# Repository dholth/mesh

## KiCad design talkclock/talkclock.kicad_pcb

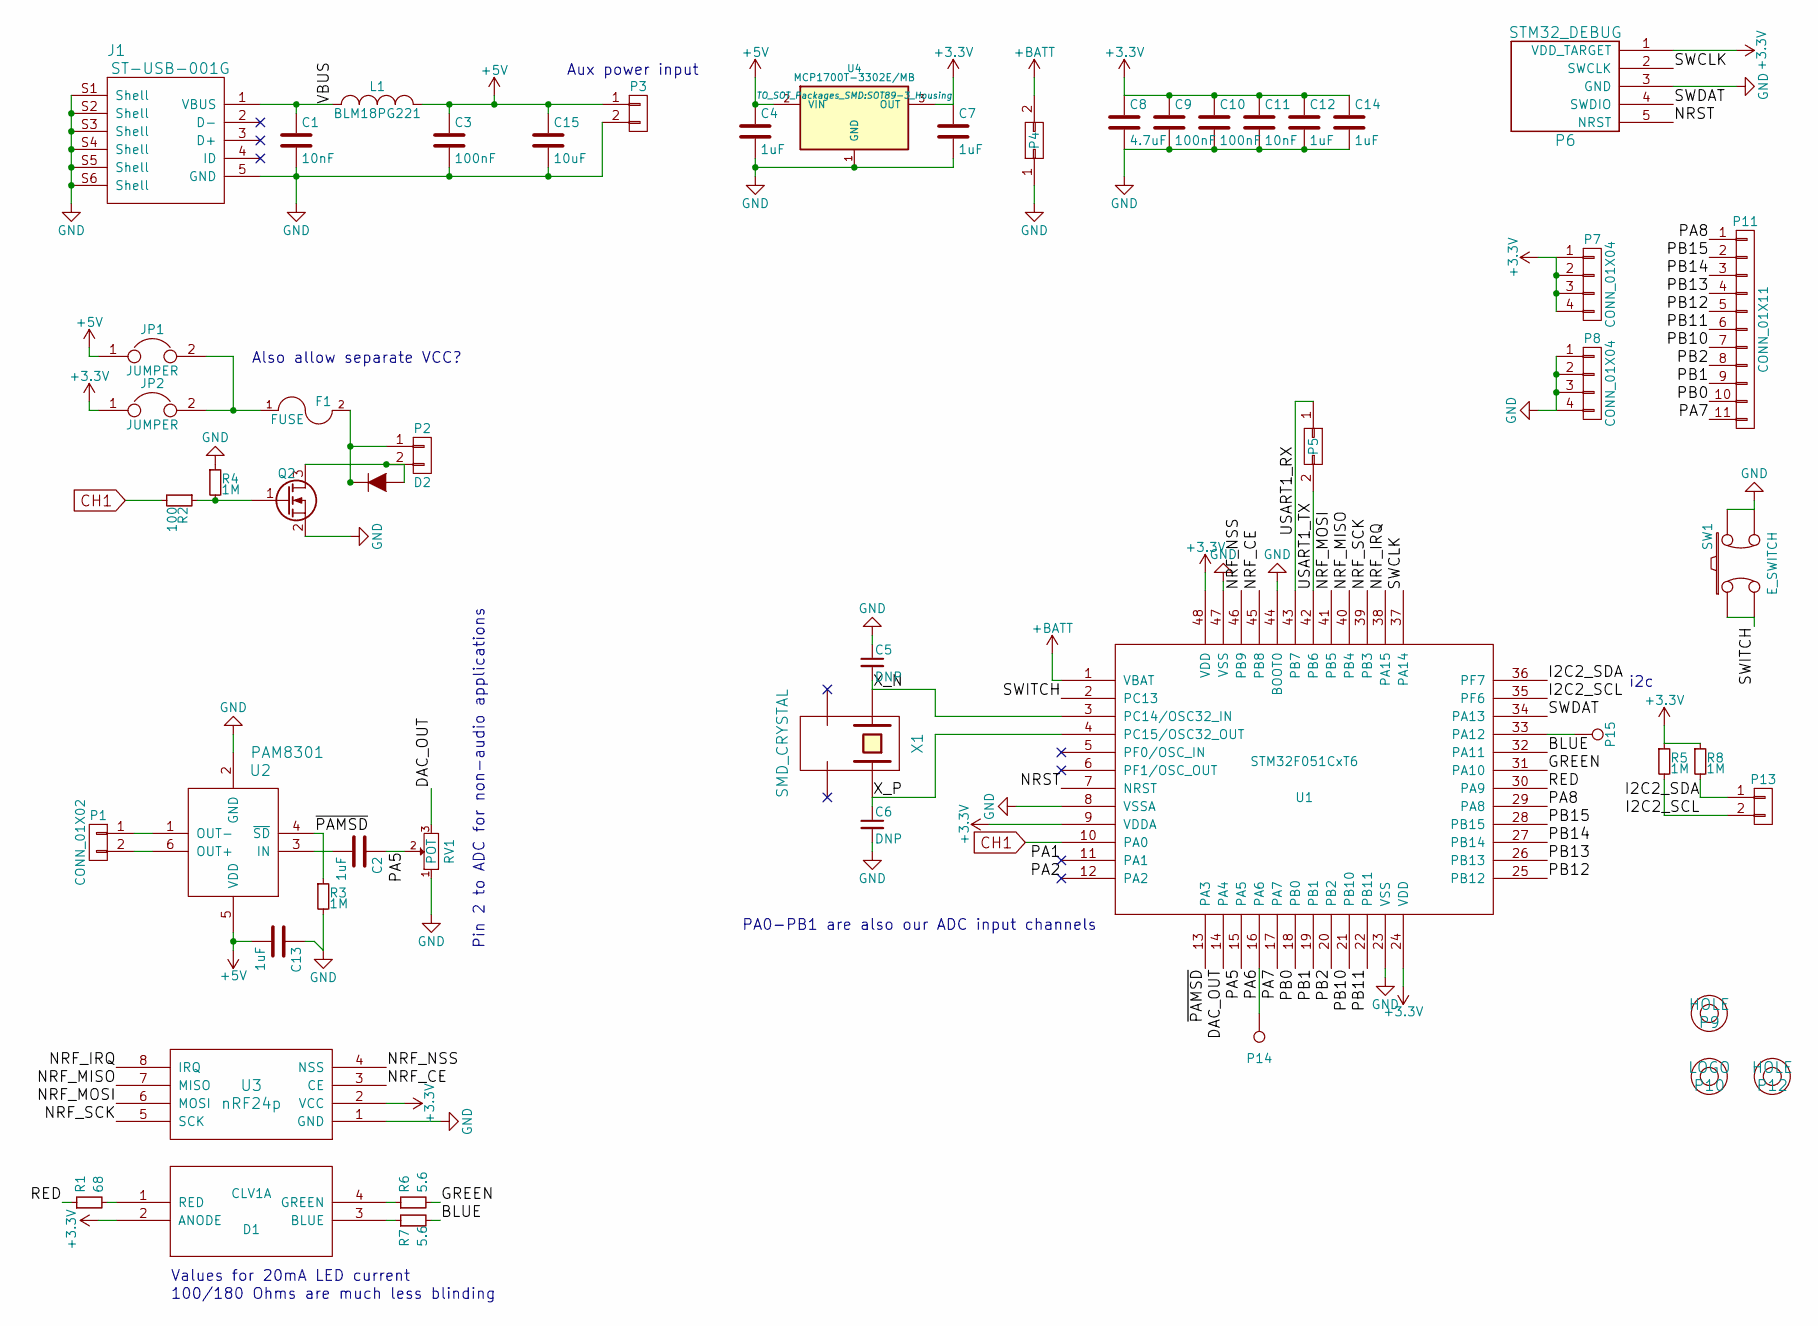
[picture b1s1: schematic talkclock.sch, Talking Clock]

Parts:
C1, C11: 10nF; C_0603
C2, C4, C7, C12, C13, C14: 1uF; C_0603
C3, C9, C10: 100nF; C_0603
C5, C6: DNP; C_0603
C8: 4.7uF; C_1206
C15: 10uF; C_Radial_D5_L11_P2
D1: CLV1A; CREE4
D2: 1N4448; SOD-323-SKYWORKS
F1: FUSE; R_1206
J1: ST-USB-001G; SUNTECH_ST-USB-001G
JP1, JP2: JUMPER; SB
L1: BLM18PG221; R_0805
P1, P13: CONN_01X02; Pin_Header_Straight_1x02
P2, P3: CONN_01X02; JST-S2B-PH
P4: CONN_02X01; BAT-HLD-012-SMT
P5: CONN_02X01; Pin_Header_Straight_1x02
P6: STM32_DEBUG; Pin_Header_Straight_1x05
P7, P8: CONN_01X04; Pin_Header_Straight_1x04
P9, P12: HOLE; MountingHole_3-2mm_DP
P10: LOGO
P11: CONN_01X11; Pin_Header_Straight_1x11
P14, P15: TEST_1P; Pin_Header_Straight_1x01_Small
Q2: Q_NMOS_GSD; SOT-23
R1: 68; R_0603
R2: 100; R_0603
R3, R4, R5, R8: 1M; R_0603
R6, R7: 5.6; R_0603
RV1: POT; EVU-F3A
SW1: E_SWITCH
U1: STM32F051CxT6; LQFP-48_7x7mm_Pitch0.5mm
U2: PAM8301; SOT-23-6
U3: nRF24p; nRF24
U4: MCP1700T-3302E/MB; SOT89-3_Housing
X1: SMD_CRYSTAL; CM200C

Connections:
+3V3: C7.1, C8.1, C9.1, C10.1, C11.1, C12.1, C14.1, D1.2 (ANODE), JP2.1, P6.1 (VDD_TARGET), P7.1, P7.2, P7.3, P7.4, R5.1, R8.1, U1.9 (VDDA), U1.24 (VDD), U1.48 (VDD), U3.2 (VCC), U4.3 (OUT)
+5V: C3.1, C4.1, C13.2, C15.1, JP1.1, L1.2, P3.1, U2.5 (VDD), U4.2 (VIN)
+BATT: P4.2, U1.1 (VBAT)
/BLUE: R7.2, U1.32 (PA11)
/DAC_OUT: RV1.3, U1.14 (PA4)
/GREEN: R6.2, U1.31 (PA10)
/I2C2_SCL: P13.2, R5.2, U1.35 (PF6)
/I2C2_SDA: P13.1, R8.2, U1.36 (PF7)
/NRF_CE: U1.45 (PB8), U3.3 (CE)
/NRF_IRQ: U1.38 (PA15), U3.8 (IRQ)
/NRF_MISO: U1.40 (PB4), U3.7 (MISO)
/NRF_MOSI: U1.41 (PB5), U3.6 (MOSI)
/NRF_NSS: U1.46 (PB9), U3.4 (NSS)
/NRF_SCK: U1.39 (PB3), U3.5 (SCK)
/NRST: P6.5 (NRST), U1.7 (NRST)
/PA5: C2.1, RV1.2, U1.15 (PA5)
/PA6: P14.1, U1.16 (PA6)
/PA7: P11.11, U1.17 (PA7)
/PA8: P11.1, U1.29 (PA8)
/PB0: P11.10, U1.18 (PB0)
/PB1: P11.9, U1.19 (PB1)
/PB2: P11.8, U1.20 (PB2)
/PB10: P11.7, U1.21 (PB10)
/PB11: P11.6, U1.22 (PB11)
/PB12: P11.5, U1.25 (PB12)
/PB13: P11.4, U1.26 (PB13)
/PB14: P11.3, U1.27 (PB14)
/PB15: P11.2, U1.28 (PB15)
/RED: R1.1, U1.30 (PA9)
/SWCLK: P6.2 (SWCLK), U1.37 (PA14)
/SWDAT: P6.4 (SWDIO), U1.34 (PA13)
/SWITCH: SW1.1, SW1.2, U1.2 (PC13)
/USART1_RX: P5.1, U1.43 (PB7)
/USART1_TX: P5.2, U1.42 (PB6)
/VBUS: C1.1, J1.1 (VBUS), L1.1
/X_N: C5.2, U1.3 (PC14/OSC32_IN), X1.4
/X_P: C6.1, U1.4 (PC15/OSC32_OUT), X1.1
/~PAMSD: R3.1, U1.13 (PA3), U2.4 (~SD)
CH1: R2.2, U1.10 (PA0)
GND: C1.2, C3.2, C4.2, C5.1, C6.2, C7.2, C8.2, C9.2, C10.2, C11.2, C12.2, C13.1, C14.2, C15.2, J1.5 (GND), J1.S1 (Shell), J1.S2 (Shell), J1.S3 (Shell), J1.S4 (Shell), J1.S5 (Shell), J1.S6 (Shell), P3.2, P4.1, P6.3 (GND), P8.1, P8.2, P8.3, P8.4, Q2.2 (S), R3.2, R4.1, RV1.1, SW1.3, SW1.4, U1.8 (VSSA), U1.23 (VSS), U1.44 (BOOT0), U1.47 (VSS), U2.2 (GND), U3.1 (GND), U4.1 (GND)
unnamed: C2.2, U2.3 (IN)
unnamed: D1.1 (RED), R1.2
unnamed: D1.3 (BLUE), R7.1
unnamed: D1.4 (GREEN), R6.1
unnamed: D2.1 (K), F1.2, P2.1
unnamed: D2.2 (A), P2.2, Q2.3 (D)
unnamed: F1.1, JP1.2, JP2.2
unnamed: P1.1, U2.1 (OUT-)
unnamed: P1.2, U2.6 (OUT+)
unnamed: P15.1, U1.33 (PA12)
unnamed: Q2.1 (G), R2.1, R4.2

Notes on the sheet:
Values for 20mA LED current
100/180 Ohms are much less blinding
i2c
PA0-PB1 are also our ADC input channels
Also allow separate VCC?
Aux power input
Pin 2 to ADC for non-audio applications

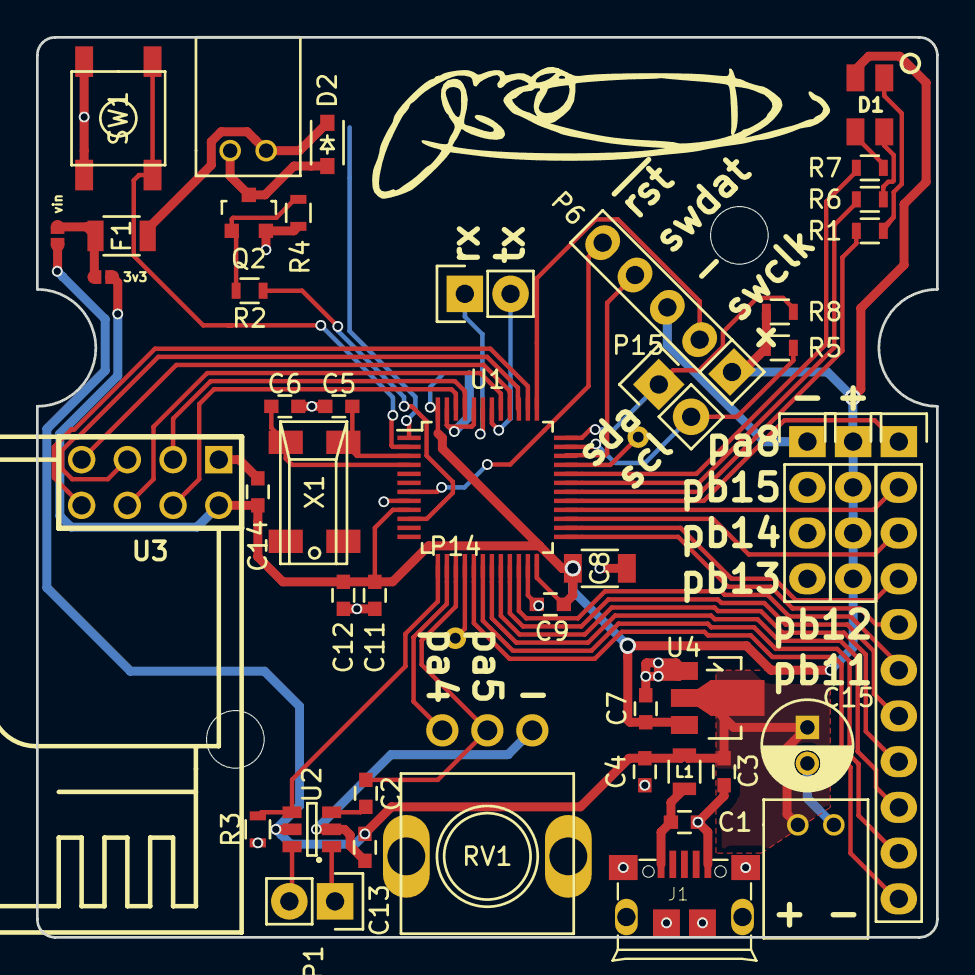
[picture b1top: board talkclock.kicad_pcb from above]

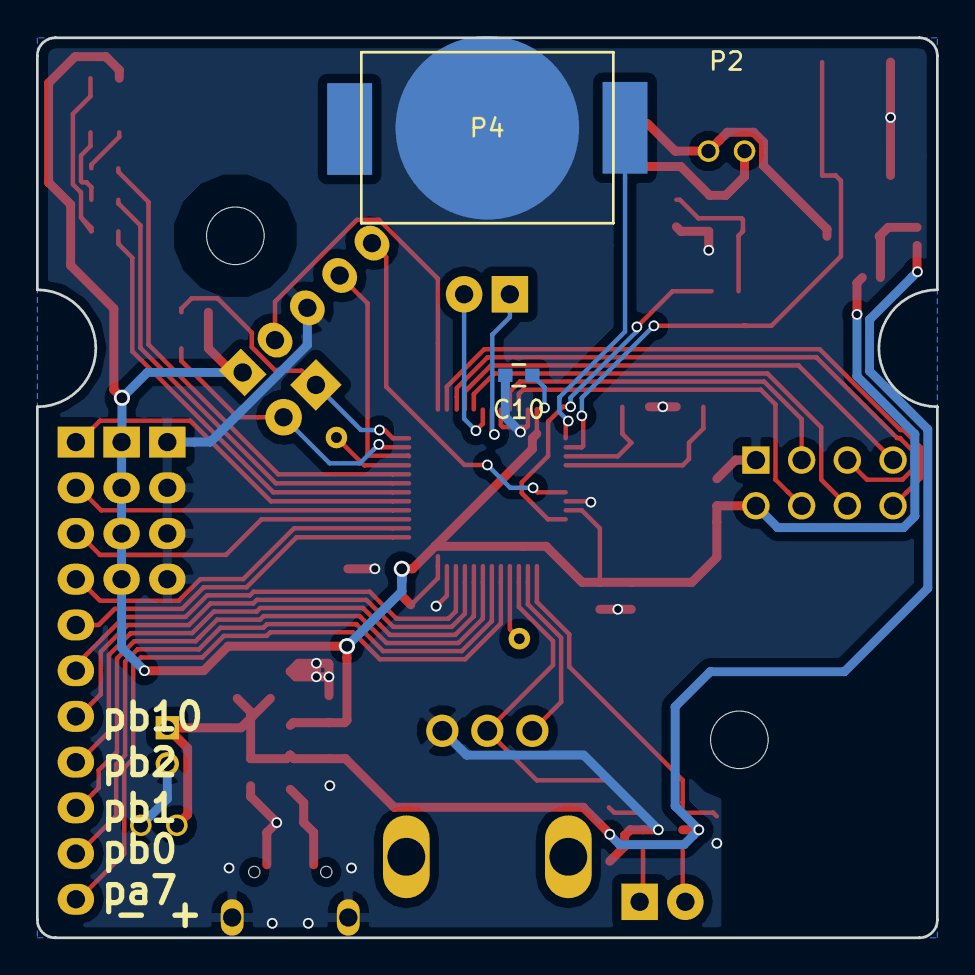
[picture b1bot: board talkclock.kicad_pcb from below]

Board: 2 copper layers, 50.0 x 50.0 mm, 53 parts (3 on the bottom side), 51 nets.

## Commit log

2017-04-28 python simulator and combination priority queue / sorted array
2017-04-28 add board files
2017-06-08 state machine to manage mac
2017-06-08 nrf24 code
2017-06-10 begin mesh API
2017-06-10 improve remove
2017-06-10 print container in order at end of test
2017-06-10 add trickle algorithm
2017-06-10 changes to compile on Linux
2017-06-11 begin copying prototype into template class
